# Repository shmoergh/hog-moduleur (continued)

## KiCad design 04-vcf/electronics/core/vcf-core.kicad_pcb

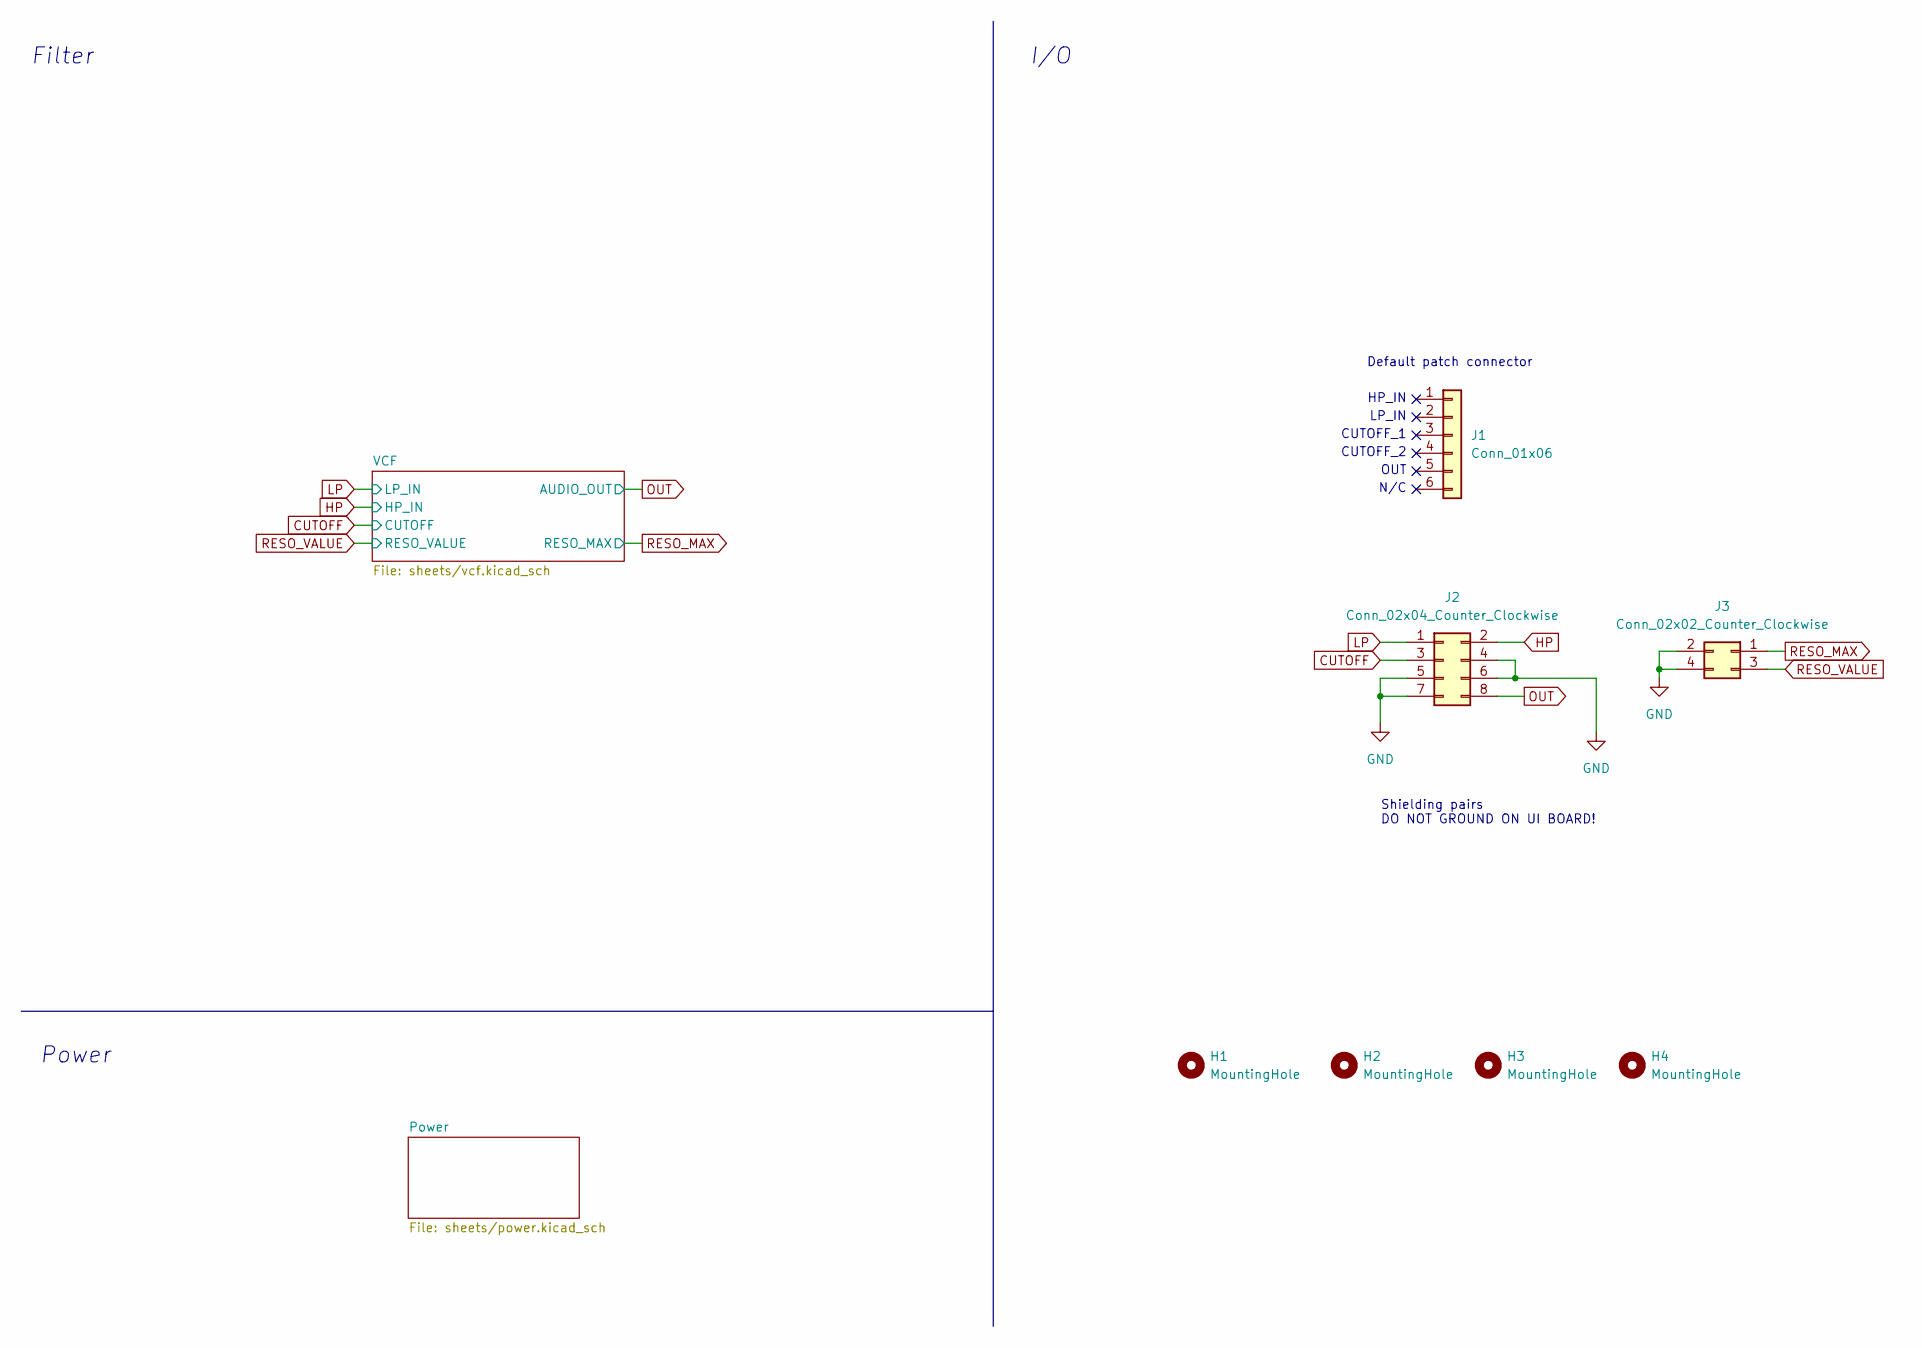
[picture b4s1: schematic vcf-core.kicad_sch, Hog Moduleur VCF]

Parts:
H1, H2, H3, H4: MountingHole; MountingHole_3.2mm_M3_DIN965_Pad
J1: Conn_01x06; PinHeader_1x06_P2.54mm_Vertical; Part no. 474-PRT-09280
J2: Conn_02x04_Counter_Clockwise; PinHeader_2x04_P2.54mm_Vertical; Part no. 200-HTSW10407TD
J3: Conn_02x02_Counter_Clockwise; PinHeader_2x02_P2.54mm_Vertical; Part no. 200-HTSW10207TD

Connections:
HP: J2.2; also elsewhere on the board
LP: J2.1; also elsewhere on the board
OUT: J2.8; also elsewhere on the board

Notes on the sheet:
Power
CUTOFF_1
Default patch connector
N/C
HP_IN
Shielding pairs DO NOT GROUND ON UI BOARD!
OUT
Filter
LP_IN
I/O
CUTOFF_2

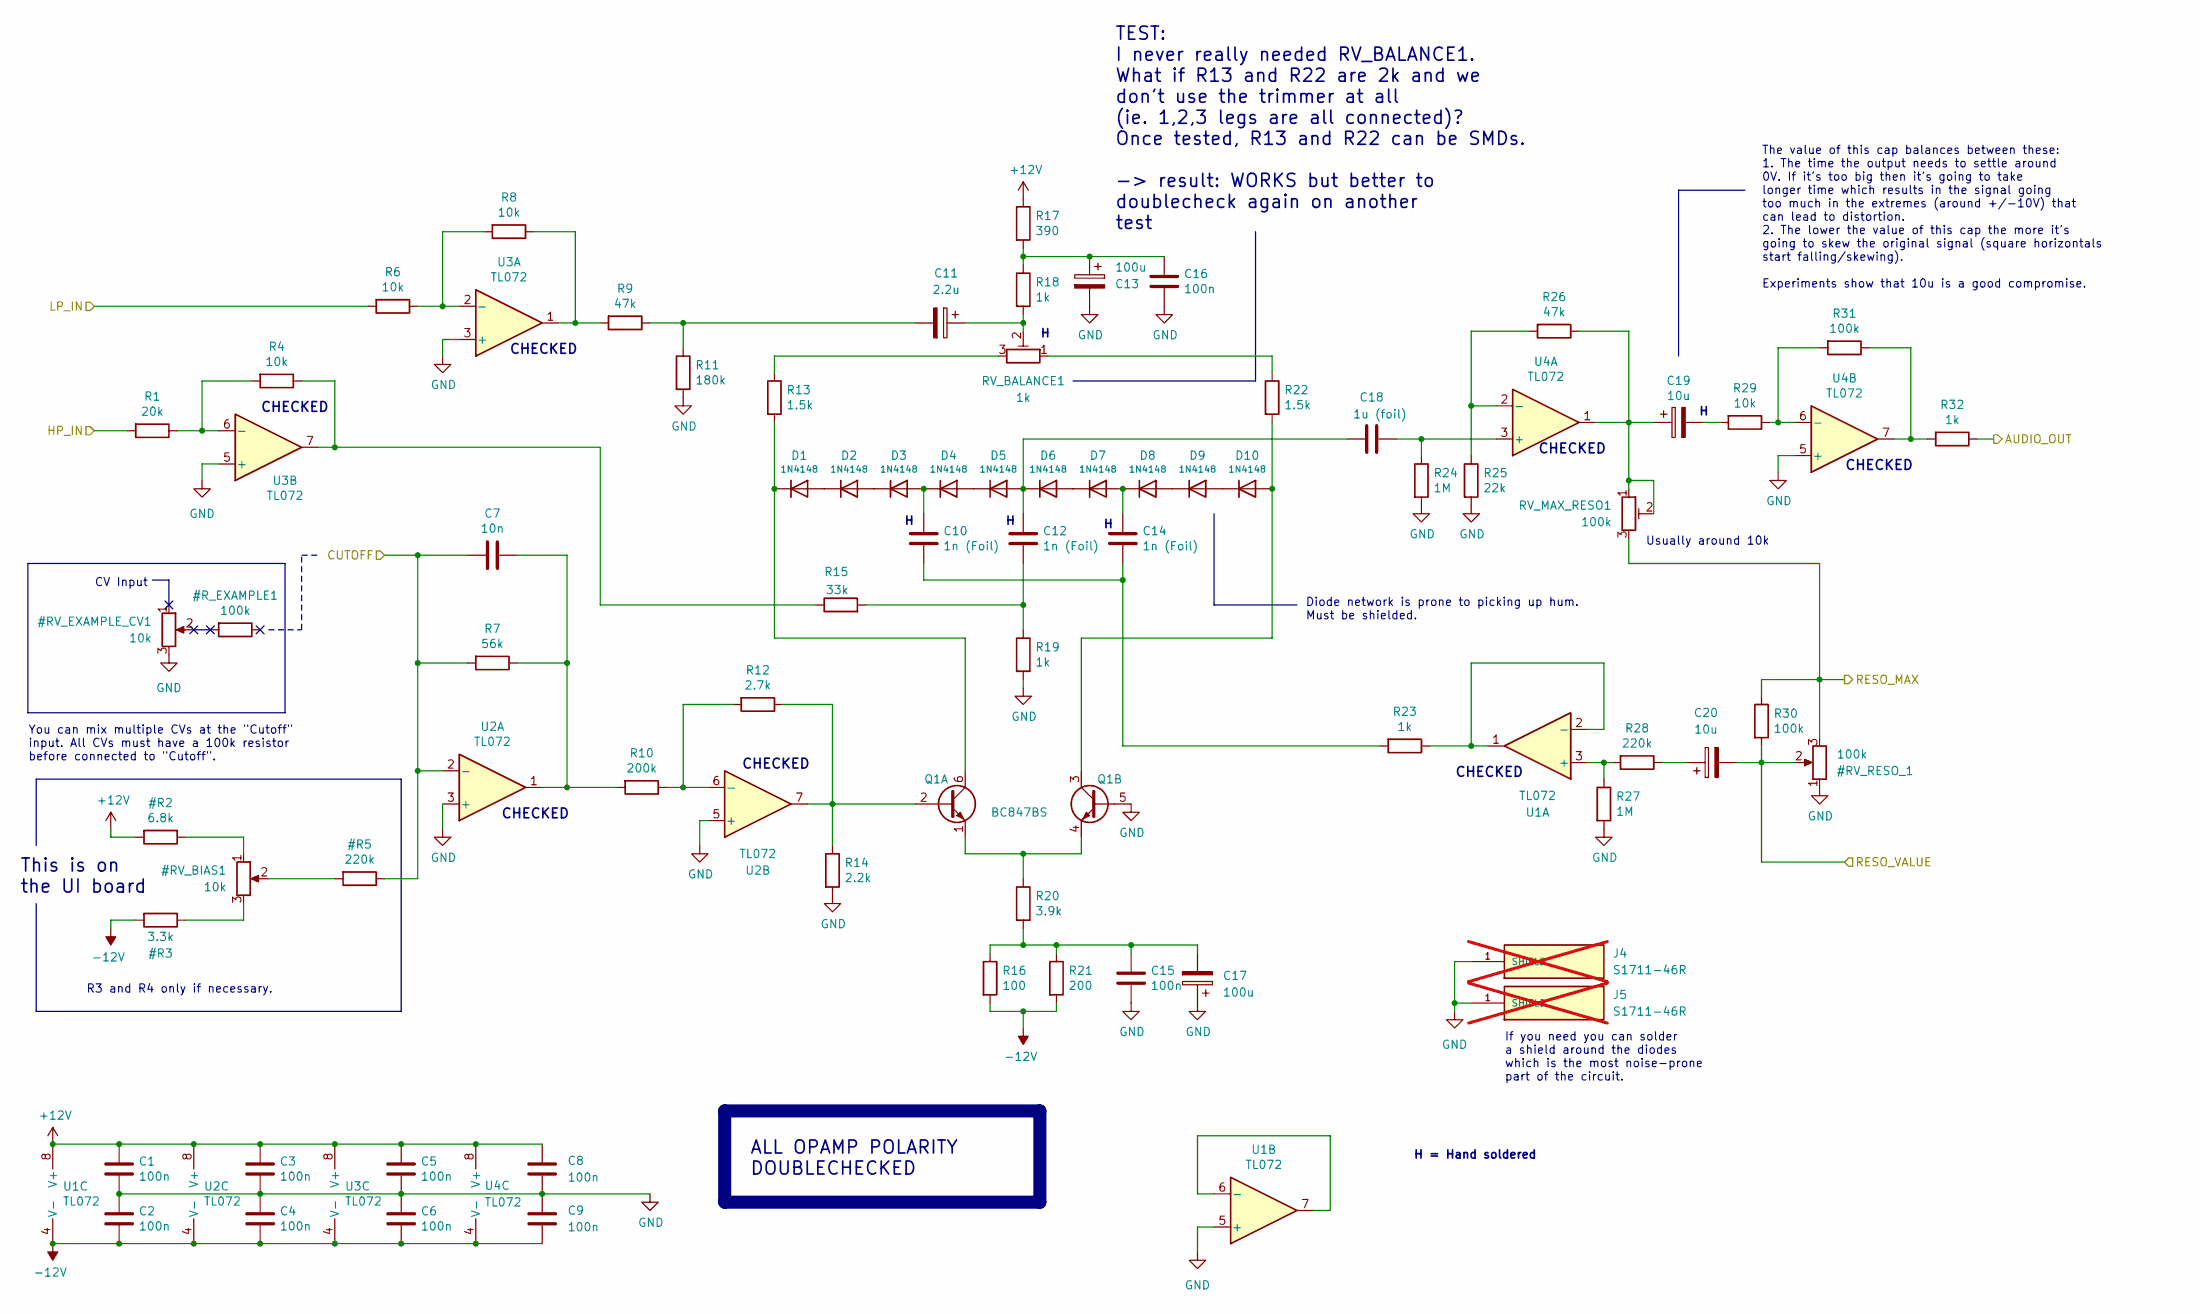
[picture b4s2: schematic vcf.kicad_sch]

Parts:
C1, C2, C3, C4, C5, C6, C8, C9, C15, C16: 100n; C_0603_1608Metric; LCSC C14663
C7: 10n; C_0603_1608Metric; LCSC C57112
C10, C12, C14: 1n (Foil); C_Rect_L7.0mm_W2.5mm_P5.00mm; Part no. 80-R82EC1100SH50J
C11: 2.2u; CP_Elec_4x5.7; LCSC C249889
C13, C17: 100u; CP_Elec_6.3x7.7; LCSC C2836437
C18: 1u (foil); C_Rect_L7.0mm_W4.5mm_P5.00mm; Part no. 80-R82EC1470DQ50K
C19: 10u; CP_Radial_D8.0mm_P5.00mm; Part no. 667-EEA-GA1V470B
C20: 10u; CP_Elec_4x5.4; LCSC C3343
D1, D2, D3, D4, D5, D6, D7, D8, D9, D10: 1N4148; D_SOD-123; LCSC C81598
J4, J5: S1711-46R; HARWIN_S1711-46R; PARTREV 23/10/18; not fitted
Q1: BC847BS; SOT-363_SC-70-6; LCSC C5380687
R1: 20k; R_0603_1608Metric_Pad0.98x0.95mm_HandSolder; LCSC C4184
R4, R6, R8, R29: 10k; R_0603_1608Metric_Pad0.98x0.95mm_HandSolder; LCSC C25804
R7: 56k; R_0603_1608Metric_Pad0.98x0.95mm_HandSolder; LCSC C23206
R9, R26: 47k; R_0603_1608Metric_Pad0.98x0.95mm_HandSolder; LCSC C25819
R10: 200k; R_0603_1608Metric_Pad0.98x0.95mm_HandSolder; LCSC C25811
R11: 180k; R_0603_1608Metric_Pad0.98x0.95mm_HandSolder; LCSC C3016400
R12: 2.7k; R_0603_1608Metric_Pad0.98x0.95mm_HandSolder; LCSC C13167
R13, R22: 1.5k; R_0603_1608Metric_Pad0.98x0.95mm_HandSolder
R14: 2.2k; R_0603_1608Metric_Pad0.98x0.95mm_HandSolder; LCSC C4190
R15: 33k; R_0603_1608Metric_Pad0.98x0.95mm_HandSolder; LCSC C4216
R16: 100; R_0603_1608Metric_Pad0.98x0.95mm_HandSolder; LCSC C22775
R17: 390; R_0603_1608Metric_Pad0.98x0.95mm_HandSolder; LCSC C23151
R18, R19, R23, R32: 1k; R_0603_1608Metric_Pad0.98x0.95mm_HandSolder; LCSC C21190
R20: 3.9k; R_0603_1608Metric_Pad0.98x0.95mm_HandSolder; LCSC C23018
R21: 200; R_0603_1608Metric_Pad0.98x0.95mm_HandSolder; LCSC C8218
R24, R27: 1M; R_0603_1608Metric_Pad0.98x0.95mm_HandSolder; LCSC C22935
R25: 22k; R_0603_1608Metric_Pad0.98x0.95mm_HandSolder; LCSC C31850
R28: 220k; R_0603_1608Metric_Pad0.98x0.95mm_HandSolder; LCSC C22961
R30, R31: 100k; R_0603_1608Metric_Pad0.98x0.95mm_HandSolder; LCSC C25803
RV_BALANCE1: 1k; Potentiometer_ACP_CA6-H2,5_Horizontal; Part no. 531-PT6KH-1K
RV_MAX_RESO1: 100k; Potentiometer_ACP_CA6-H2,5_Horizontal; Part no. 531-PT6KH104A1010PM
U1, U2, U3, U4: TL072; SOIC-8_3.9x4.9mm_P1.27mm; LCSC C6961

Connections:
HP: R1.2; also elsewhere on the board
LP: R6.2; also elsewhere on the board
unnamed: C7.1, R7.1, R10.2, U2.1
unnamed: C10.2, C14.2, R23.2
unnamed: C11.1, R18.2, RV_BALANCE1.2
unnamed: C11.2, R9.1, R11.1
unnamed: C12.2, R15.2, R19.1
unnamed: C13.1, C16.1, R17.2, R18.1
unnamed: C15.1, C17.2, R16.1, R20.2, R21.1
unnamed: C19.1, R26.1, RV_MAX_RESO1.1, RV_MAX_RESO1.2, U4.1
unnamed: C19.2, R29.2
unnamed: C20.1, R28.1
unnamed: D1.2 (A), D2.1 (K)
unnamed: D1.1 (K), Q1.6 (C1), R13.2
unnamed: D2.2 (A), D3.1 (K)
unnamed: C10.1, D3.2 (A), D4.1 (K)
unnamed: D4.2 (A), D5.1 (K)
unnamed: C12.1, C18.2, D5.2 (A), D6.1 (K)
unnamed: D6.2 (A), D7.1 (K)
unnamed: C14.1, D7.2 (A), D8.1 (K)
unnamed: D8.2 (A), D9.1 (K)
unnamed: D10.2 (A), Q1.3 (C2), R22.2
unnamed: D9.2 (A), D10.1 (K)
unnamed: Q1.2 (B1), R12.1, R14.1, U2.7
unnamed: Q1.1 (E1), Q1.4 (E2), R20.1
unnamed: R8.1, R9.2, U3.1
unnamed: R13.1, RV_BALANCE1.3
unnamed: R4.1, R15.1, U3.7
unnamed: R22.1, RV_BALANCE1.1
unnamed: R31.1, R32.2, U4.7
unnamed: R27.1, R28.2, U1.3 (+)
unnamed: R23.1, U1.1, U1.2 (-)
unnamed: U1.6 (-), U1.7
unnamed: R10.1, R12.2, U2.6 (-)
unnamed: R6.1, R8.2, U3.2 (-)
unnamed: R1.1, R4.2, U3.6 (-)
unnamed: C18.1, R24.1, U4.3 (+)
unnamed: R25.1, R26.2, U4.2 (-)
unnamed: R29.1, R31.2, U4.6 (-)
OUT: R32.1; also elsewhere on the board

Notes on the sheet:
R3 and R4 only if necessary.
CHECKED
CV Input
If you need you can solder a shield around the diodes which is the most noise-prone part of the circuit.
ALL OPAMP POLARITY DOUBLECHECKED
This is on the UI board
Diode network is prone to picking up hum. Must be shielded.
You can mix multiple CVs at the "Cutoff" input. All CVs must have a 100k resistor before connected to "Cutoff".
The value of this cap balances between these: 1. The time the output needs to settle around 0V. If it's too big then it's going to take longer time which results in the signal going too much in the extremes (around +/-10V) that can lead to distortion. 2. The lower the value of this cap the more it'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
Usually around 10k
H = Hand soldered
TEST: I never really needed RV_BALANCE1. What if R13 and R22 are 2k and we don't use the trimmer at all (ie. 1,2,3 legs are all connected)? Once tested, R13 and R22 can be SMDs. -> result: WORKS but better to doublecheck again on another test

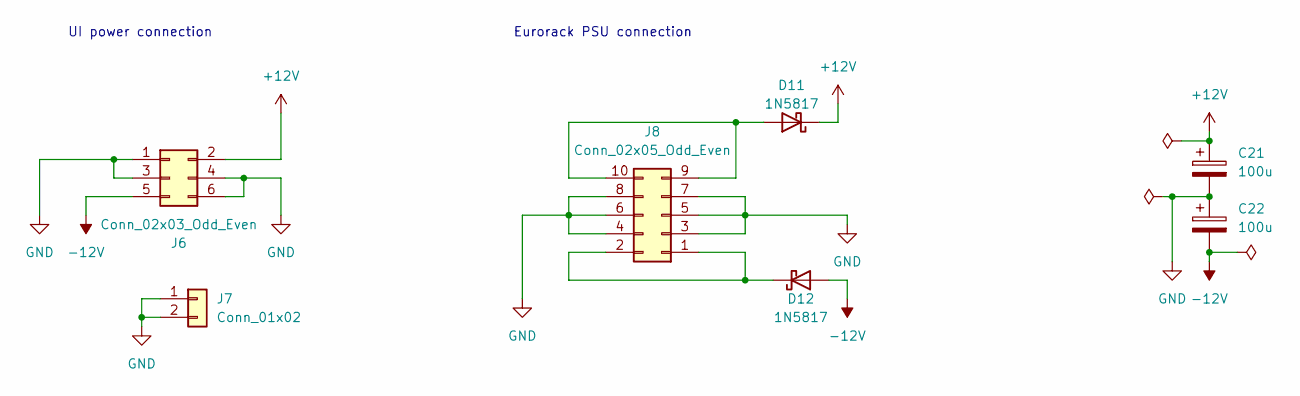
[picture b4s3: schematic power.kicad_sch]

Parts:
C21, C22: 100u; CP_Elec_6.3x7.7; LCSC C2836437
D11, D12: 1N5817; D_SOD-323; LCSC C5190152
J6: Conn_02x03_Odd_Even; PinHeader_2x03_P2.54mm_Vertical; Part no. 200-TSW10307TD
J7: Conn_01x02; PinHeader_1x02_P2.54mm_Vertical; Part no. 200-HTSW10207TS
J8: Conn_02x05_Odd_Even; IDC-Header_2x05_P2.54mm_Horizontal; Part no. 571-5103310-1

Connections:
unnamed: D11.2 (A), J8.9, J8.10
unnamed: D12.1 (K), J8.1, J8.2

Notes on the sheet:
UI power connection
Eurorack PSU connection

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
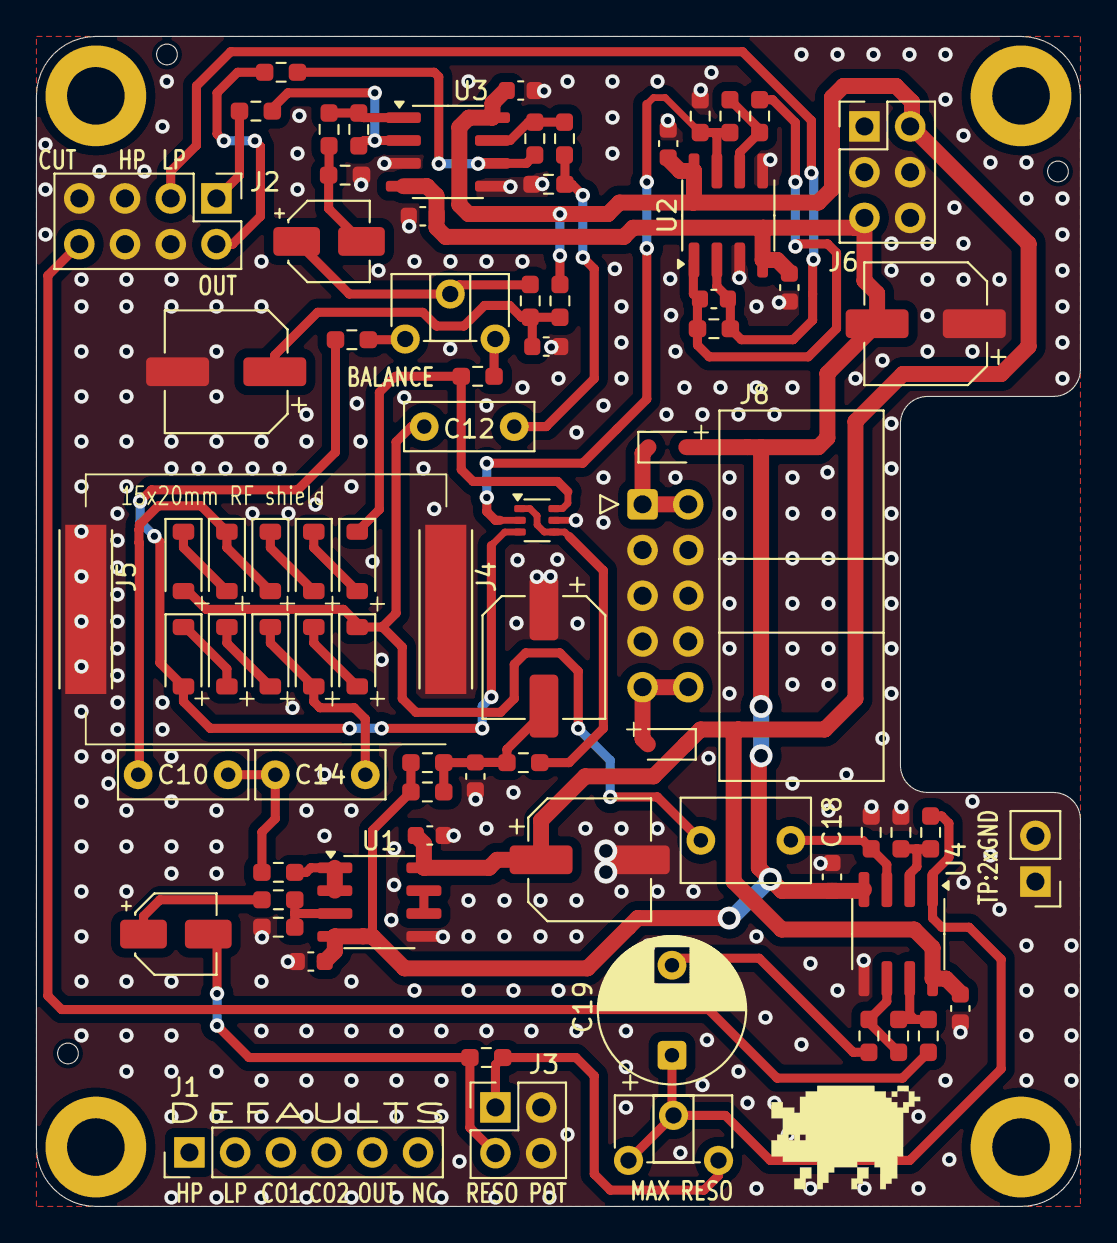
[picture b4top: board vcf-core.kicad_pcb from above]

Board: 2 copper layers, 58.0 x 65.0 mm, 82 parts (0 on the bottom side), 48 nets.

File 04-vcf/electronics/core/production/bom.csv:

Designator,Footprint,Quantity,Value,LCSC Part #
"C1, C15, C16, C2, C3, C4, C5, C6, C8, C9",0603,10,100n,C14663
"C10, C12, C14",C_Rect_L7.0mm_W2.5mm_P5.00mm,3,1n (Foil),
C11,CP_Elec_4x5.7,1,2.2u,C249889
"C13, C17, C21, C22",CP_Elec_6.3x7.7,4,100u,C2836437
C18,C_Rect_L7.0mm_W3.5mm_P5.00mm,1,470n (foil),
C19,C_Rect_L7.0mm_W4.5mm_P5.00mm,1,1u (Foil),
C20,CP_Elec_4x5.4,1,10u,C3343
C7,0603,1,10n,C57112
"D1, D10, D2, D3, D4, D5, D6, D7, D8, D9",D_SOD-123,10,1N4148,C81598
"D11, D12",D_SOD-323,2,1N5817,C5190152
J1,PinHeader_1x06_P2.54mm_Vertical,1,Conn_01x06,
J2,PinHeader_2x04_P2.54mm_Vertical,1,Conn_02x04_Counter_Clockwise,
J3,PinHeader_2x02_P2.54mm_Vertical,1,Conn_02x02_Counter_Clockwise,
J6,PinHeader_2x03_P2.54mm_Vertical,1,Conn_02x03_Odd_Even,
J7,PinHeader_1x02_P2.54mm_Vertical,1,Conn_01x02,
J8,IDC-Header_2x05_P2.54mm_Horizontal,1,Conn_02x05_Odd_Even,
Q1,SOT-363_SC-70-6,1,BC847BS,C5380687
R1,0603,1,20k,C4184
R10,0603,1,200k,C25811
R11,0603,1,180k,C3016400
R12,0603,1,2.7k,C13167
"R13, R22",R_Axial_DIN0207_L6.3mm_D2.5mm_P7.62mm_Horizontal,2,2k,
R14,0603,1,2.2k,C4190
R15,0603,1,33k,C4216
R16,0603,1,100,C22775
R17,0603,1,390,C23151
"R18, R19, R23, R32",0603,4,1k,C21190
R20,0603,1,3.9k,C23018
R21,0603,1,200,C8218
"R24, R27",0603,2,1M,C22935
R25,0603,1,22k,C31850
"R26, R9",0603,2,47k,C25819
R28,0603,1,220k,C22961
"R29, R4, R6, R8",0603,4,10k,C25804
"R30, R31",0603,2,100k,C25803
R7,0603,1,56k,C23206
RV_BALANCE1,"Potentiometer_ACP_CA6-H2,5_Horizontal",1,1k,
RV_MAX_RESO1,"Potentiometer_ACP_CA6-H2,5_Horizontal",1,100k,
"U1, U2, U3, U4",SOIC-8_3.9x4.9mm_P1.27mm,4,TL072,C6961

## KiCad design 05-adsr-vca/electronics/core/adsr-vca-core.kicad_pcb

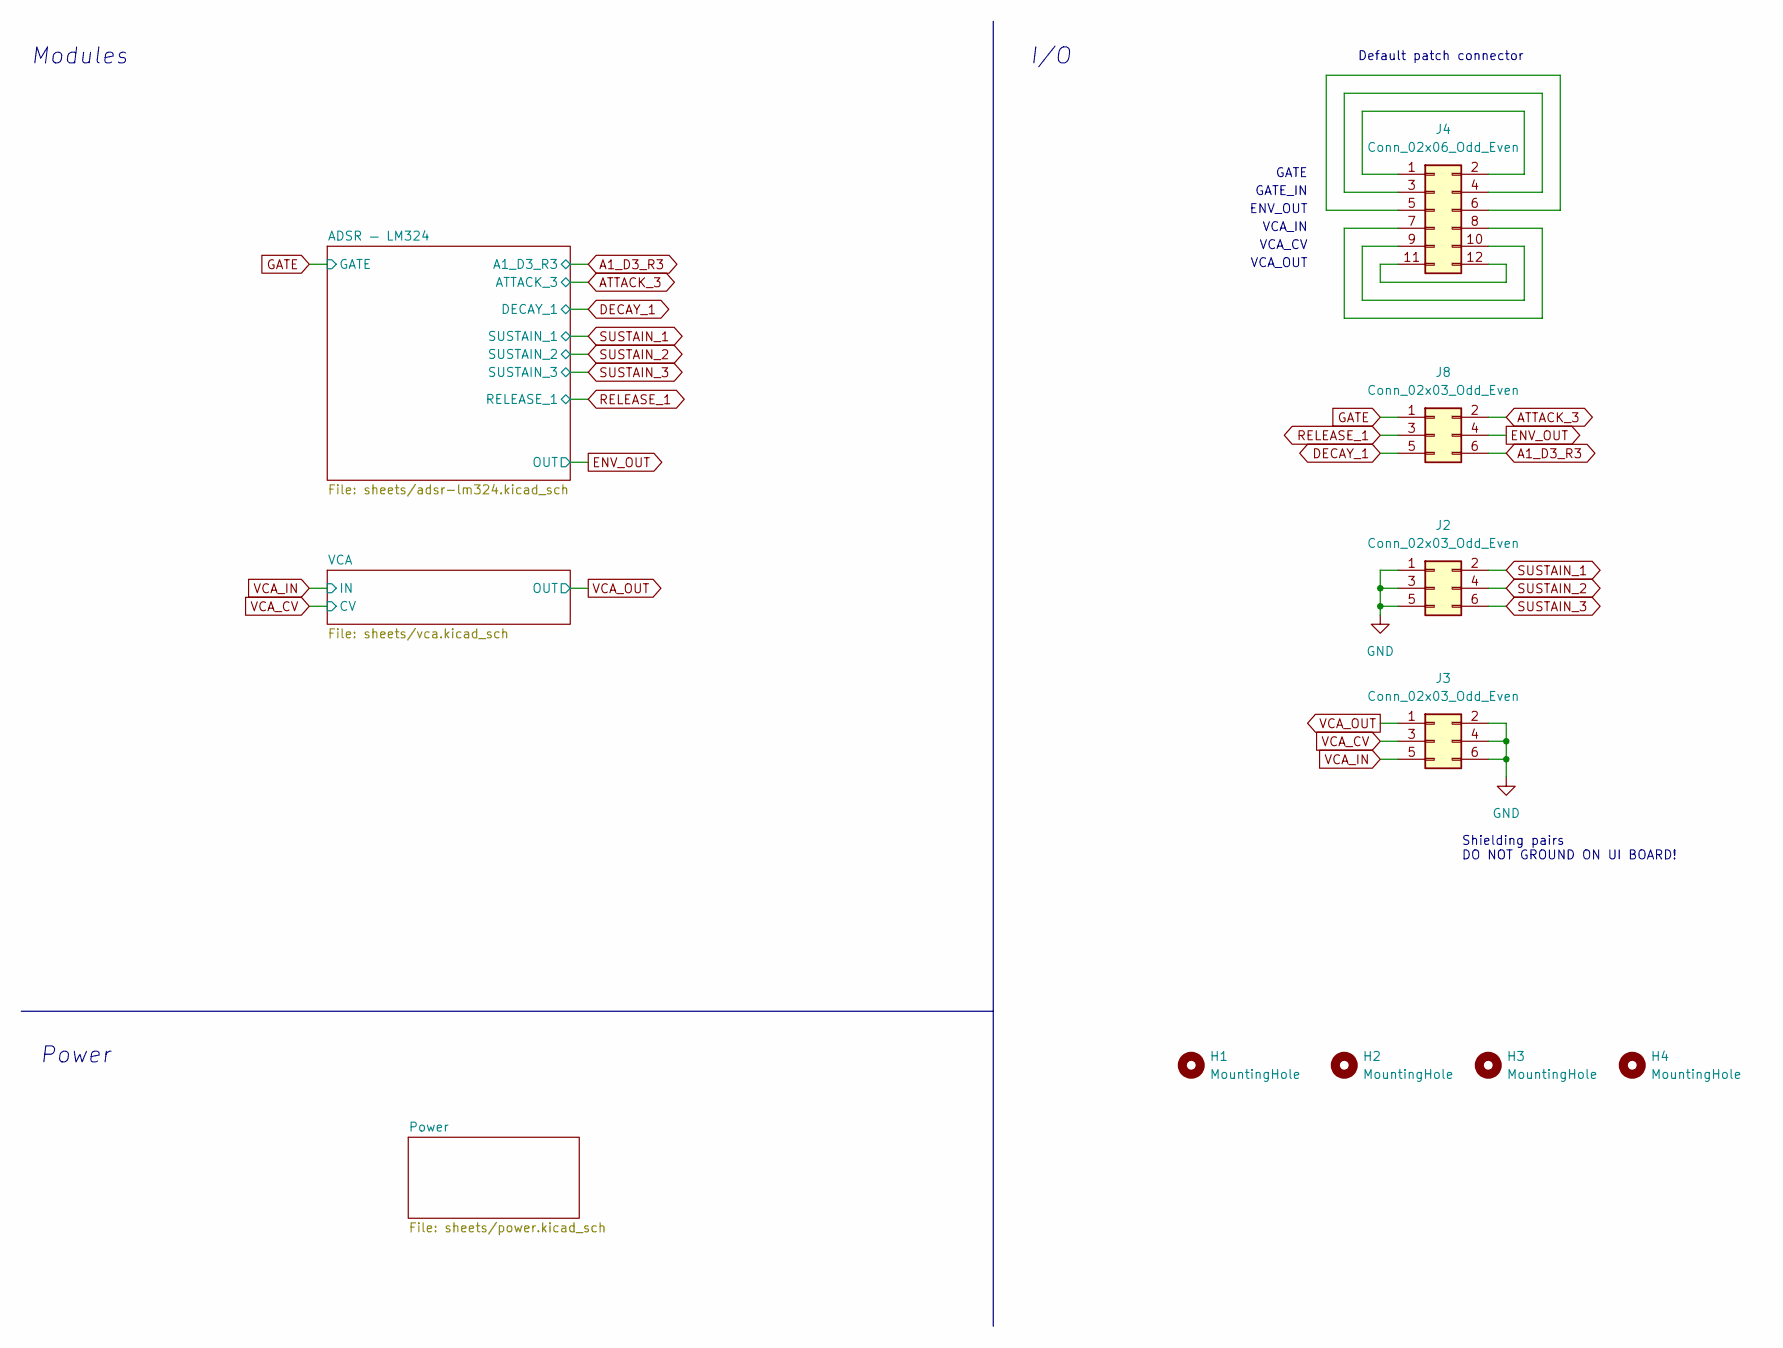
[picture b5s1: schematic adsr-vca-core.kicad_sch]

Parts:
H1, H2, H3, H4: MountingHole; MountingHole_3.2mm_M3_DIN965_Pad
J2, J3, J8: Conn_02x03_Odd_Even; PinHeader_2x03_P2.54mm_Vertical
J4: Conn_02x06_Odd_Even; PinHeader_2x06_P2.54mm_Vertical

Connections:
A1_D3_R3: J8.6; also elsewhere on the board
ATTACK_3: J8.2; also elsewhere on the board
DECAY_1: J8.5; also elsewhere on the board
ENV_OUT: J8.4; also elsewhere on the board
GATE: J8.1; also elsewhere on the board
GND: J2.1, J2.3, J2.5, J3.2, J3.4, J3.6; also elsewhere on the board
unnamed: J4.1, J4.2
unnamed: J4.3, J4.4
unnamed: J4.5, J4.6
unnamed: J4.7, J4.8
unnamed: J4.9, J4.10
unnamed: J4.11, J4.12
RELEASE_1: J8.3; also elsewhere on the board
SUSTAIN_1: J2.2; also elsewhere on the board
SUSTAIN_2: J2.4; also elsewhere on the board
SUSTAIN_3: J2.6; also elsewhere on the board
VCA_CV: J3.3; also elsewhere on the board
VCA_IN: J3.5; also elsewhere on the board
VCA_OUT: J3.1; also elsewhere on the board

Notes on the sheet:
Power
ENV_OUT
Default patch connector
VCA_OUT
GATE
Shielding pairs DO NOT GROUND ON UI BOARD!
VCA_CV
Modules
GATE_IN
I/O
VCA_IN

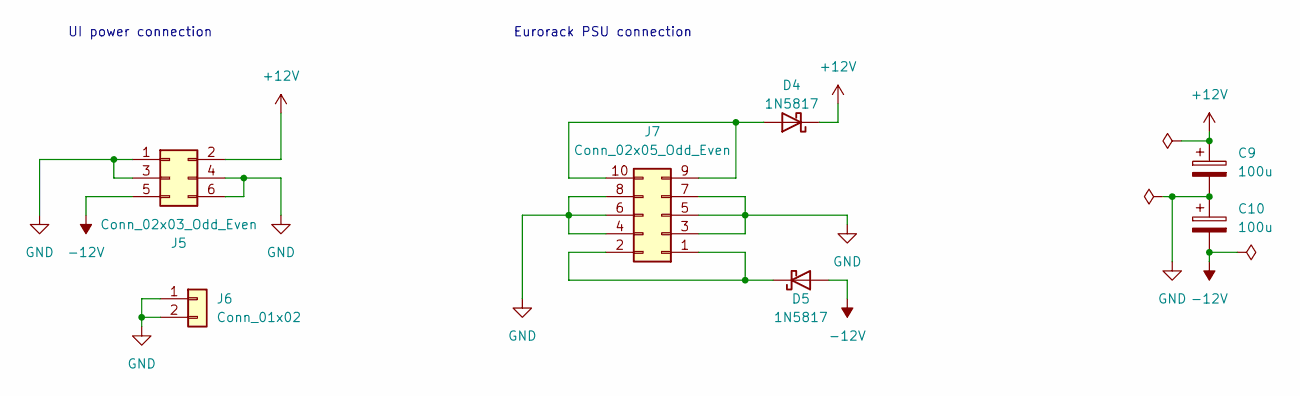
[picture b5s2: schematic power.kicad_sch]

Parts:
C9, C10: 100u; CP_Elec_6.3x7.7; LCSC C2836437
D4, D5: 1N5817; D_SOD-323; LCSC C5190152
J5: Conn_02x03_Odd_Even; PinHeader_2x03_P2.54mm_Vertical
J6: Conn_01x02; PinHeader_1x02_P2.54mm_Vertical
J7: Conn_02x05_Odd_Even; IDC-Header_2x05_P2.54mm_Horizontal

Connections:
+12V: C9.1, D4.1 (K), J5.2; also elsewhere on the board
-12V: C10.2, D5.2 (A), J5.5; also elsewhere on the board
GND: C9.2, C10.1, J5.1, J5.3, J5.4, J5.6, J6.1, J6.2, J7.3, J7.4, J7.5, J7.6, J7.7, J7.8; also elsewhere on the board
unnamed: D4.2 (A), J7.9, J7.10
unnamed: D5.1 (K), J7.1, J7.2

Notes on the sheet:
UI power connection
Eurorack PSU connection

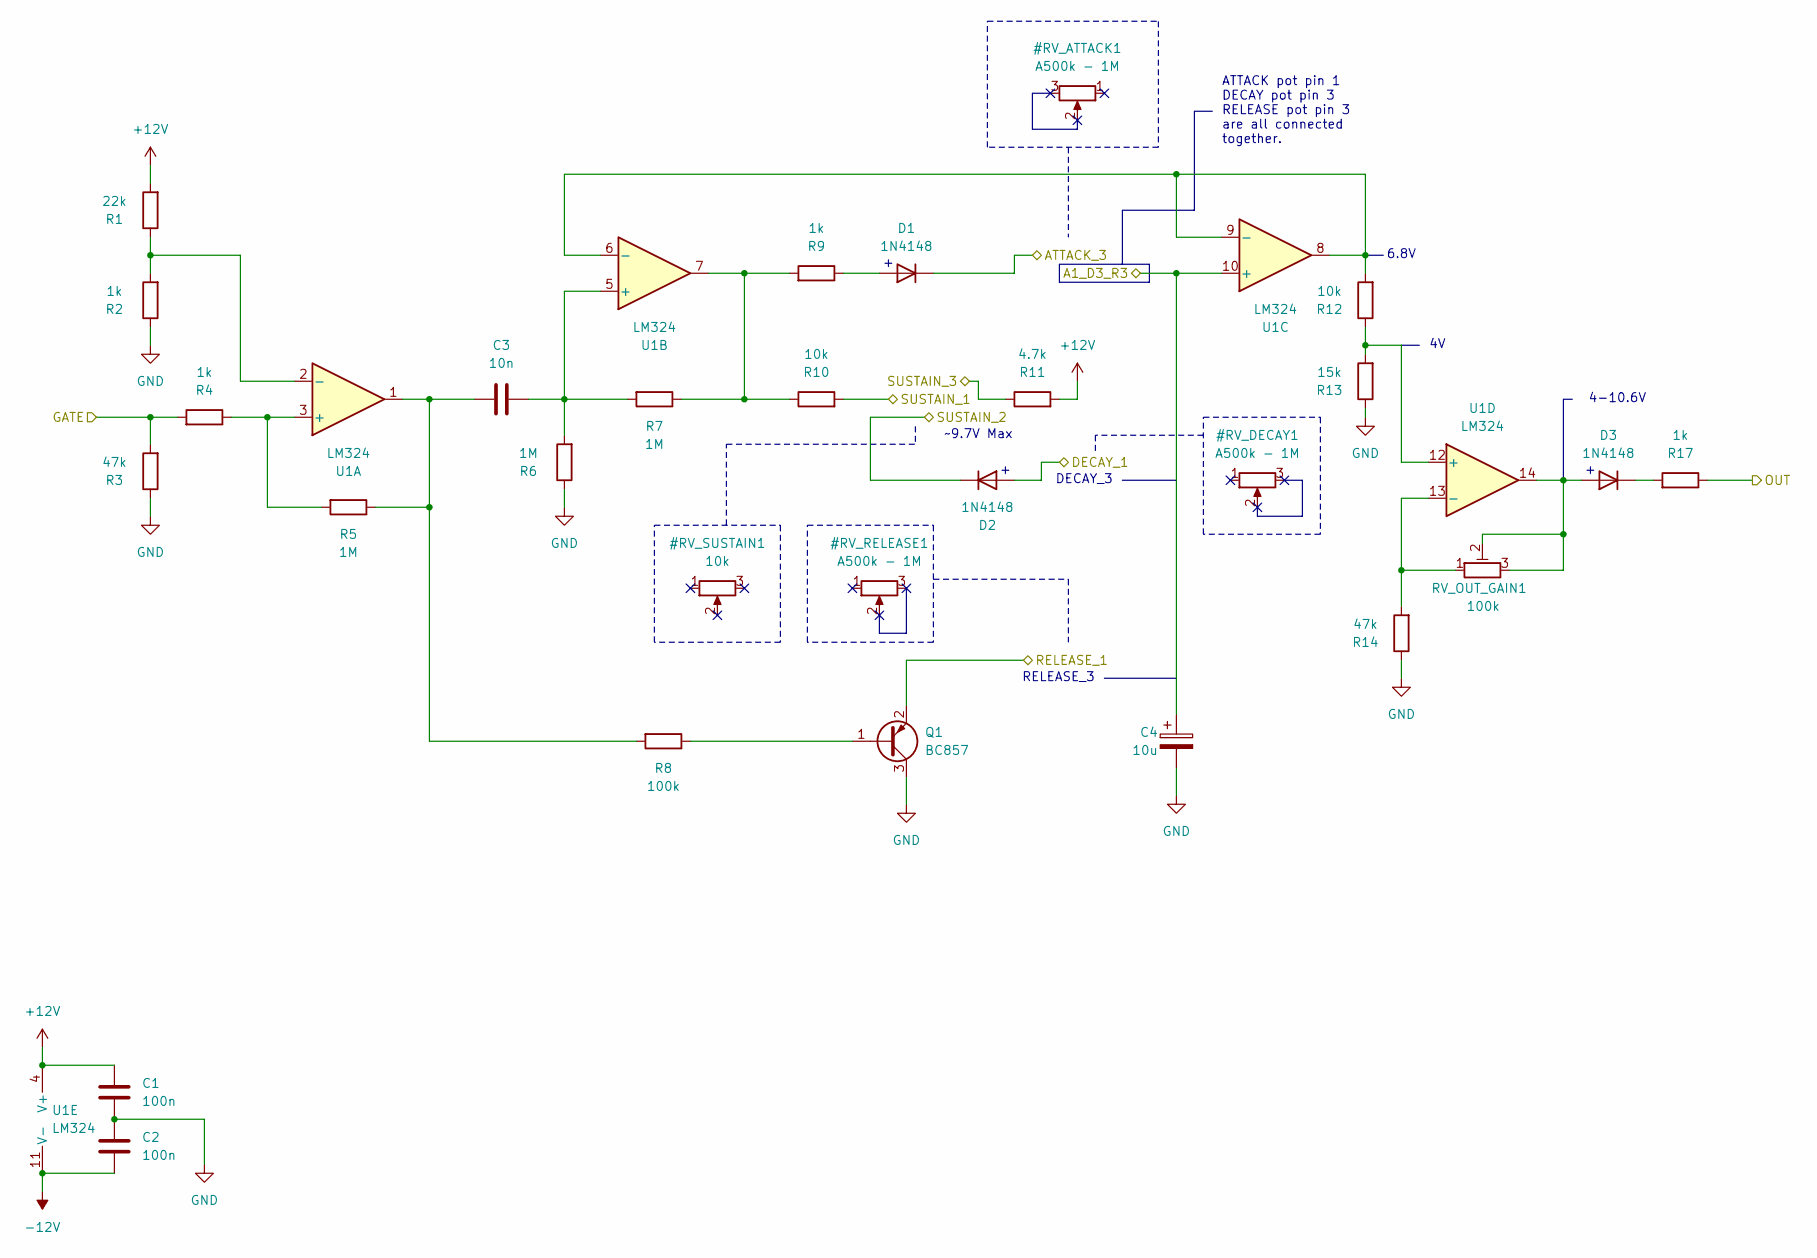
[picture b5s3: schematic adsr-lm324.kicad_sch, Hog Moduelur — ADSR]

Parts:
C1, C2: 100n; C_0603_1608Metric; LCSC C14663
C3: 10n; C_0603_1608Metric; LCSC C57112
C4: 10u; CP_Elec_5x5.4; LCSC C30110
D1, D2, D3: 1N4148; D_SOD-123; LCSC C81598
Q1: BC857; SOT-23; LCSC C20069137
R1: 22k; R_0603_1608Metric; LCSC C31850
R2, R4, R9, R17: 1k; R_0603_1608Metric; LCSC C21190
R3, R14: 47k; R_0603_1608Metric; LCSC C25819
R5, R6, R7: 1M; R_0603_1608Metric; LCSC C22935
R8: 100k; R_0603_1608Metric; LCSC C25803
R10, R12: 10k; R_0603_1608Metric; LCSC C25804
R11: 4.7k; R_0603_1608Metric; LCSC C23162
R13: 15k; R_0603_1608Metric; LCSC C22809
RV_OUT_GAIN1: 100k; Potentiometer_ACP_CA6-H2,5_Horizontal
U1: LM324; SOIC-14_3.9x8.7mm_P1.27mm; LCSC C71035

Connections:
+12V: C1.1, R1.2, R11.2, U1.4 (V+); also elsewhere on the board
-12V: C2.2, U1.11 (V-); also elsewhere on the board
A1_D3_R3: C4.1, U1.10 (+); also elsewhere on the board
ATTACK_3: D1.1 (K); also elsewhere on the board
DECAY_1: D2.2 (A); also elsewhere on the board
ENV_OUT: R17.1; also elsewhere on the board
GATE: R3.2, R4.2; also elsewhere on the board
GND: C1.2, C2.1, C4.2, Q1.3 (C), R2.1, R3.1, R6.1, R13.1, R14.1; also elsewhere on the board
unnamed: C3.1, R5.1, R8.2, U1.1
unnamed: D1.2 (A), R9.1
unnamed: D3.2 (A), RV_OUT_GAIN1.2, RV_OUT_GAIN1.3, U1.14
unnamed: D3.1 (K), R17.2
unnamed: Q1.1 (B), R8.1
unnamed: R7.1, R9.2, R10.1, U1.7
unnamed: R4.1, R5.2, U1.3 (+)
unnamed: R1.1, R2.2, U1.2 (-)
unnamed: C3.2, R6.2, R7.2, U1.5 (+)
unnamed: R12.2, U1.6 (-), U1.8, U1.9 (-)
unnamed: R12.1, R13.2, U1.12 (+)
unnamed: R14.2, RV_OUT_GAIN1.1, U1.13 (-)
RELEASE_1: Q1.2 (E); also elsewhere on the board
SUSTAIN_1: R10.2; also elsewhere on the board
SUSTAIN_2: D2.1 (K); also elsewhere on the board
SUSTAIN_3: R11.1; also elsewhere on the board

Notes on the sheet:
4-10.6V
DECAY_3
~9.7V Max
RELEASE_3
6.8V
ATTACK pot pin 1 DECAY pot pin 3 RELEASE pot pin 3 are all connected together.

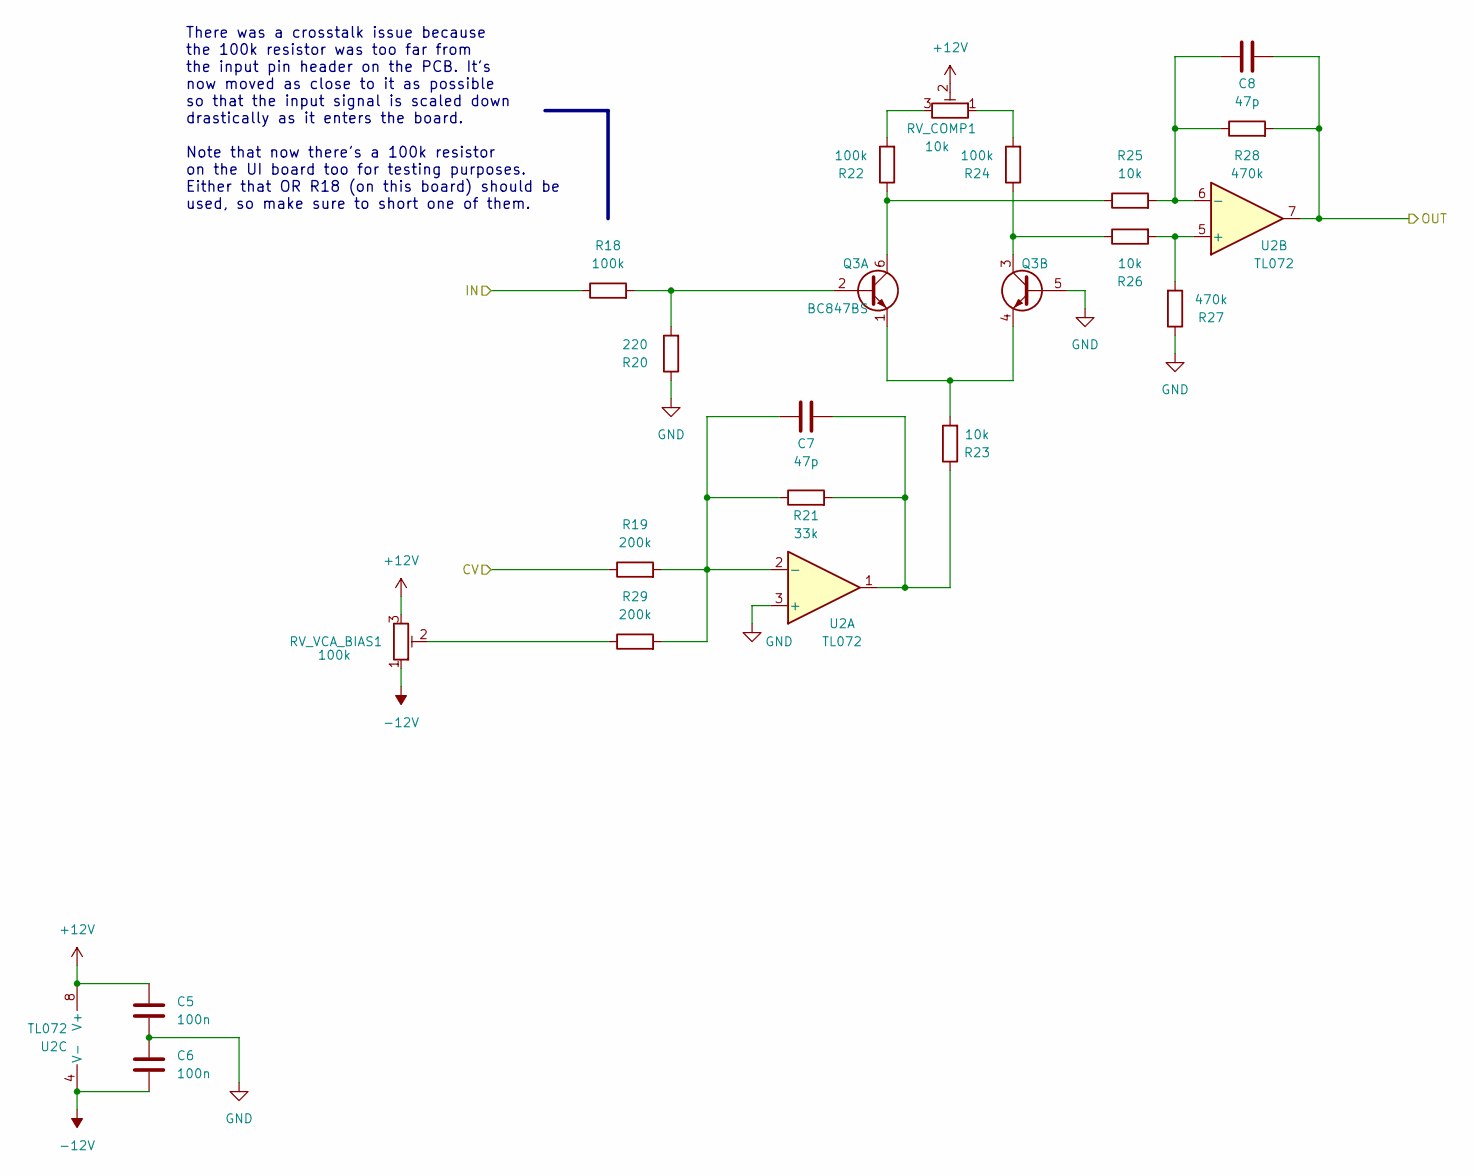
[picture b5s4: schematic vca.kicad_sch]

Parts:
C5, C6: 100n; C_0603_1608Metric; LCSC C14663
C7, C8: 47p; C_0603_1608Metric_Pad1.08x0.95mm_HandSolder; LCSC C1671
Q3: BC847BS; SOT-363_SC-70-6; LCSC C5380687
R18, R22, R24: 100k; R_0603_1608Metric; LCSC C25803
R19, R29: 200k; R_0603_1608Metric; LCSC C25811
R20: 220; R_0603_1608Metric; LCSC C22962
R21: 33k; R_0603_1608Metric; LCSC C4216
R23, R25, R26: 10k; R_0603_1608Metric; LCSC C25804
R27, R28: 470k; R_0603_1608Metric; LCSC C23178
RV_COMP1: 10k; Potentiometer_ACP_CA6-H2,5_Horizontal
RV_VCA_BIAS1: 100k; Potentiometer_ACP_CA6-H2,5_Horizontal
U2: TL072; SOIC-8_3.9x4.9mm_P1.27mm; LCSC C6961

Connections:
+12V: C5.1, RV_COMP1.2, RV_VCA_BIAS1.3, U2.8 (V+); also elsewhere on the board
-12V: C6.2, RV_VCA_BIAS1.1, U2.4 (V-); also elsewhere on the board
GND: C5.2, C6.1, Q3.5 (B2), R20.1, R27.1, U2.3 (+); also elsewhere on the board
unnamed: C7.2, R21.2, R23.1, U2.1
unnamed: Q3.2 (B1), R18.2, R20.2
unnamed: Q3.6 (C1), R22.1, R25.1
unnamed: Q3.1 (E1), Q3.4 (E2), R23.2
unnamed: Q3.3 (C2), R24.1, R26.1
unnamed: R22.2, RV_COMP1.3
unnamed: R24.2, RV_COMP1.1
unnamed: R29.1, RV_VCA_BIAS1.2
unnamed: C7.1, R19.2, R21.1, R29.2, U2.2 (-)
unnamed: R26.2, R27.2, U2.5 (+)
unnamed: C8.1, R25.2, R28.1, U2.6 (-)
VCA_CV: R19.1; also elsewhere on the board
VCA_IN: R18.1; also elsewhere on the board
VCA_OUT: C8.2, R28.2, U2.7; also elsewhere on the board

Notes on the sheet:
There was a crosstalk issue because the 100k resistor was too far from the input pin header on the PCB. It's now moved as close to it as possible so that the input signal is scaled down drastically as it enters the board. Note that now there's a 100k resistor on the UI board too for testing purpose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
